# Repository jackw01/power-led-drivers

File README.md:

# power-led-drivers

## Features

### boostdriver-AL8853 rev1

* Input voltage range: 6-40V
* Input current up to 3A, higher current possible with cooling
* Output voltage up to 80V, higher voltage possible with modifications
* Up to 93% efficient at 20V input, ~75V 50W output
* Based on the [Diodes Incorporated AL8853 boost controller](https://www.diodes.com/assets/Datasheets/AL8853.pdf)
* Optional onboard USB-C power input (>50W output from USB without a heatsink)
* PWM input for brightness control
* Optional onboard dimmer for self-contained standalone use

## Design

### boostdriver-AL8853 rev1

[Schematic as PDF](pcb/schematic%20rev1%2020230619-01.pdf)

## Component Selection

Component selections should be based on the <a href="https://www.diodes.com/assets/Calculators/AL8853-Calculator.xlsx">AL8853 Design Calculator spreadsheet</a> provided by Diodes Incorporated.

For most applications, the components shown in the schematic can be left as-is except for the inductor and current sense resistor. Molded composite inductors are strongly recommended, and physically larger inductors will generally provide better efficiency and thermal performance. The switching FET listed in the schematic may be out of stock, but many suitable parts are available. The PCB footprint will accommodate a 3.3mm DFN package; [this DigiKey search](https://www.digikey.com/en/products/filter/transistors-fets-mosfets-single/278?s=N4IgjCBcoGwJxVAYygMwIYBsDOBTANCAPZQDaIALAAxwDMdIh1cFtVIAuoQA4AuUIAMq8ATgEsAdgHMQAX0IwqMRCBSQMOAsTIhaAdgAccY5x79IQ0ZJnzwAJjgRoqtFjyESkchTp2ArMqEDvQsjCAO1GB%2BYRFUYIHhLHG0MSxgeilBaQZ6qRRgDFkUFAYQRSV2eXp%2BZYkU1Zl1pblFpQitdrUReo55cDAtdXAZqX5Ufo0Ufn4UDqO0FAkOE-rzPvM5YbS0BtQUWzvUBmFTPXaN27tg7IQLYG1bAROVtzD1doNTcGMXBjB2ii2fwBtRKBnOtR2-3%2BJ0uoVuwJgv2G5xO4No-iBLD8xwRLD0N10RneWMW7SJLG%2BWL8H2pbGpczxzzpk3SH2iTAKxVZLHqJy5JROnX6uS4ID4AmE4mkciCSmOzjUGnc2i84CoVAABAA1Uzi8wgACqEjEvAA8qgALK4dDYACuIlwspAAFoEIqoKI7VpPOQIBxbC7Kh7IF6fTpogHZLIgA) shows compatible parts.

More detailed information on component selection is provided in the annotations in the schematic.

### License
This project is released under the CERN Open Hardware Licence Version 2 - Weakly Reciprocal (CERN-OHL-W V2).

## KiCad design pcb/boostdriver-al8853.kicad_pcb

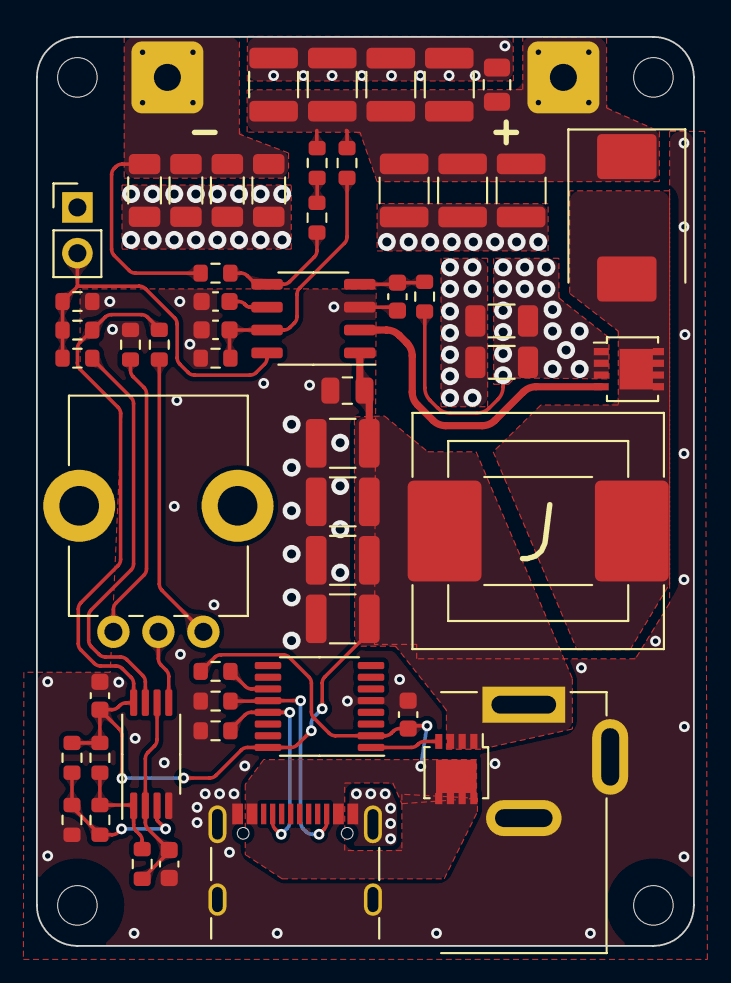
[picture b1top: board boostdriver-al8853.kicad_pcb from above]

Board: 2 copper layers, 36.5 x 50.5 mm, 61 parts (0 on the bottom side), 25 nets.

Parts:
C101, C102, C103, C104, C106, C108, C110: 4.7u; C_1210_3225Metric
C105, C107, C109, C111: 10u; C_1210_3225Metric
C112: 0.1u; C_0805_2012Metric
C113, C116: -; C_0603_1608Metric
C114: 1u; C_0805_2012Metric
C115: 0.1u; C_0603_1608Metric
C201: 1u; C_0603_1608Metric
C301: 100n; C_0603_1608Metric
C302: 1n; C_0603_1608Metric
D101: SS310; D_SMC
H101, H102, H103, H104: MountingHole; MountingHole_2.2mm_M2_Mask
J101, J102: Conn_01x01_Pin; SolderWire-4x4
J103: Conn_01x02; PinHeader_1x02_P2.54mm_Vertical
J201: RAPC732X; BarrelJack_GCT_DCJ200-10-A_Horizontal
J202: USB_C_Receptacle_USB2.0; USB_C_Receptacle_GCT_USB4105-xx-A_16P_TopMnt_Horizontal
L101: 22u; L_12mm_multi
Q101, Q201: DMT10H015LFG-7; LFPAK33
R101, R102, R103, R112, R115: 0; R_0603_1608Metric
R104, R105, R106, R107: 0.3; R_1206_3216Metric
R108: 475k; R_0603_1608Metric
R109, R114: 15k; R_0603_1608Metric
R110: -; R_1206_3216Metric
R111: 0.02; R_1206_3216Metric
R113, R203: 100k; R_0603_1608Metric
R201, R202: 5.1k; R_0603_1608Metric
R301, R302, R306, R307: 31.6k; R_0603_1608Metric
R303, R304: 24.9k; R_0603_1608Metric
R305: 2.49k; R_0603_1608Metric
RV301: 100k; Potentiometer_Bourns_PTV09A-1_Single_Vertical
U101: AL8853; SO-8_3.9x4.9mm_P1.27mm
U201: IP2721; TSSOP-16_4.4x5mm_P0.65mm
U301: LM393APWR; TSSOP-8_4.4x3mm_P0.65mm

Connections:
/CS: Q101.1 (S), Q101.2 (S), Q101.3 (S), R110.1, R111.1, R112.1
/FB: R102.1, R103.2, U101.5 (FB)
/GATE: Q101.4 (G), U101.2 (GATE)
/LED+: C101.1, C102.1, C103.1, C104.1, C106.1, C108.1, C110.1, C112.1, D101.1 (K), J101.1, R101.2, R108.1
/LED-: J102.1, R103.1, R104.1, R105.1, R106.1, R107.1
/LX: D101.2 (A), L101.1, Q101.5 (D)
/OVP: C116.2, R108.2, R109.1, U101.7 (OVP)
/PWM_IN: J103.2, R113.2, R114.1, R115.2, U101.8 (PWM)
/VIN_DRV: C105.1, C107.1, C109.1, C111.1, C114.1, C301.1, J201.1, L101.2, Q201.1 (S), Q201.2 (S), Q201.3 (S), R113.1, R301.1, R305.1, R306.1, U101.1 (VIN), U201.16 (VBUS), U301.8 (V+)
/pwm_generator/PWM: R115.1, U301.7
GND: C101.2, C102.2, C103.2, C104.2, C105.2, C106.2, C107.2, C108.2, C109.2, C110.2, C111.2, C112.2, C113.1, C114.2, C115.1, C116.1, C201.1, C301.2, C302.2, J103.1, J201.2, J201.3, J202.A1 (GND), J202.A12 (GND), J202.B1 (GND), J202.B12 (GND), J202.S1 (SHIELD), R104.2, R105.2, R106.2, R107.2, R109.2, R110.2, R111.2, R114.2, R201.2, R202.2, R302.2, R307.2, U101.3 (GND), U201.5 (GND), U301.4 (V-)
unnamed: J202.A5 (CC1), R202.1, U201.13 (CC1)
unnamed: J202.B5 (CC2), R201.1, U201.12 (CC2)
unnamed: C201.2, J202.A4 (VBUS), J202.A9 (VBUS), J202.B4 (VBUS), J202.B9 (VBUS), Q201.5 (D), R203.1, U201.2 (VIN)
unnamed: Q201.4 (G), U201.1 (VBUSG)
unnamed: R101.1, R102.2
unnamed: R303.2, R304.2, R305.2, U301.1
unnamed: R306.2, RV301.1
unnamed: R307.1, RV301.3
unnamed: C115.2, U101.6 (COMP)
unnamed: C113.2, R112.2, U101.4 (CS)
unnamed: R203.2, U201.11 (SEL)
unnamed: R301.2, R302.1, R303.1, U301.3 (+)
unnamed: C302.1, R304.1, U301.2 (-), U301.6 (-)
unnamed: RV301.2, U301.5 (+)

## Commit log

2023-06-19 add images
2023-06-19 add boostdriver
2023-06-25 add pcb and schematic files
2025-03-06 Update LICENSE

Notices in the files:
pcb/boostdriver-al8853.kicad_pcb:
Released under the CERN-OHL-W V2 license
